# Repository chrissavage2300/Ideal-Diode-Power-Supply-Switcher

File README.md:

# Ideal-Diode-Power-Supply-Switcher
Ideal diode switcher based on two LM66200DRLR

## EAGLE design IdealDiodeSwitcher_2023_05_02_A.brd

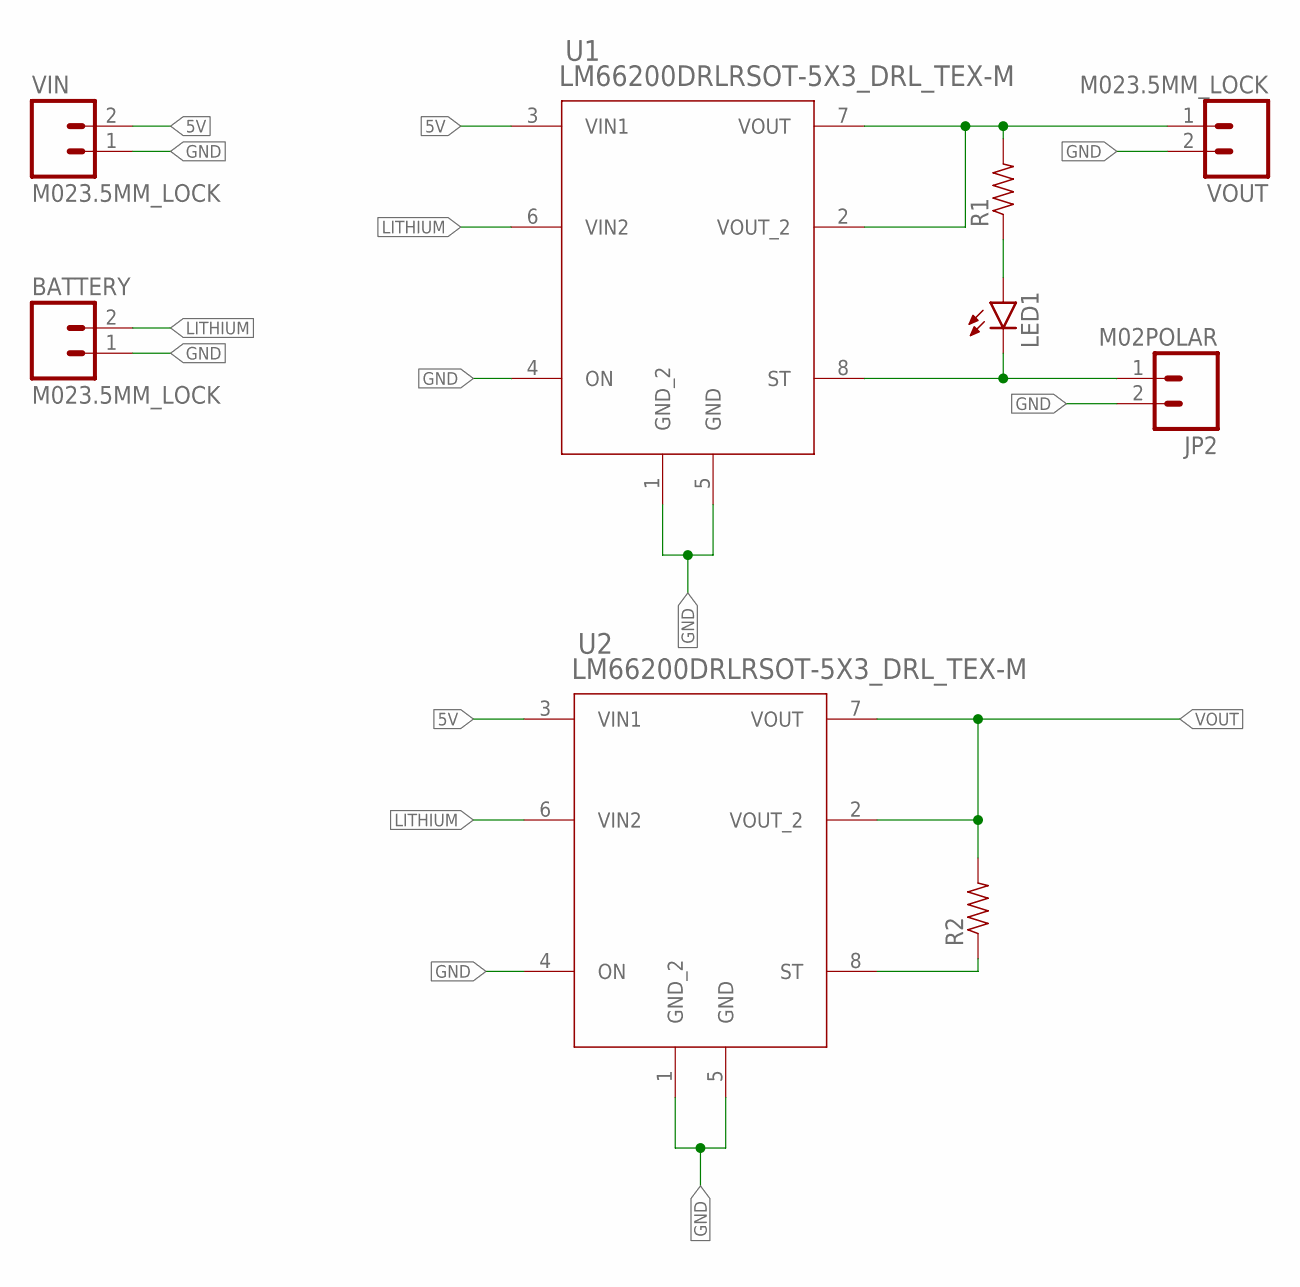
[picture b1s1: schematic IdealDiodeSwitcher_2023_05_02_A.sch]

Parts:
BATTERY: M023.5MM_LOCK; SCREWTERMINAL-3.5MM-2_LOCK
JP2: M02POLAR; MOLEX-1X2
LED1: LED1206; LED-1206
R1, R2: RESISTOR1206; 1206
U1, U2: LM66200DRLRSOT-5X3_DRL_TEX-M; SOT-5X3_DRL_TEX-M
VIN: M023.5MM_LOCK; SCREWTERMINAL-3.5MM-2_LOCK
VOUT: M023.5MM_LOCK; SCREWTERMINAL-3.5MM-2_LOCK

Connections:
5V: U1.3 (VIN1), U2.3 (VIN1), VIN.2
GND: BATTERY.1, JP2.2, U1.1 (GND_2), U1.4 (ON), U1.5 (GND), U2.1 (GND_2), U2.4 (ON), U2.5 (GND), VIN.1, VOUT.2
LITHIUM: BATTERY.2, U1.6 (VIN2), U2.6 (VIN2)
unnamed: LED1.A, R1.1
STAT: JP2.1, LED1.C, U1.8 (ST)
STAT1: R2.1, U2.8 (ST)
VOUT: R1.2, R2.2, U1.2 (VOUT_2), U1.7 (VOUT), U2.2 (VOUT_2), U2.7 (VOUT), VOUT.1

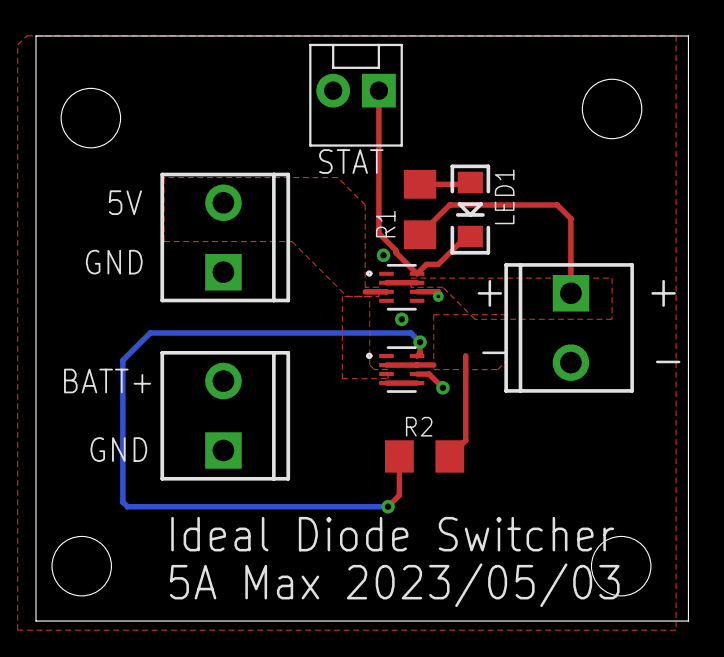
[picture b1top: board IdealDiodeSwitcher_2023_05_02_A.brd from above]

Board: 2 copper layers, 36.2 x 32.5 mm, 9 parts (0 on the bottom side), 7 nets.

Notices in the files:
parts and their libraries:
SparkFun-Connectors: Licensing: Creative Commons ShareAlike 4.0 International - https://creativecommons.org/licenses/by-sa/4.0
COPYRIGHT: Copyright (C) 2023 Ultra Librarian. All rights reserved.
